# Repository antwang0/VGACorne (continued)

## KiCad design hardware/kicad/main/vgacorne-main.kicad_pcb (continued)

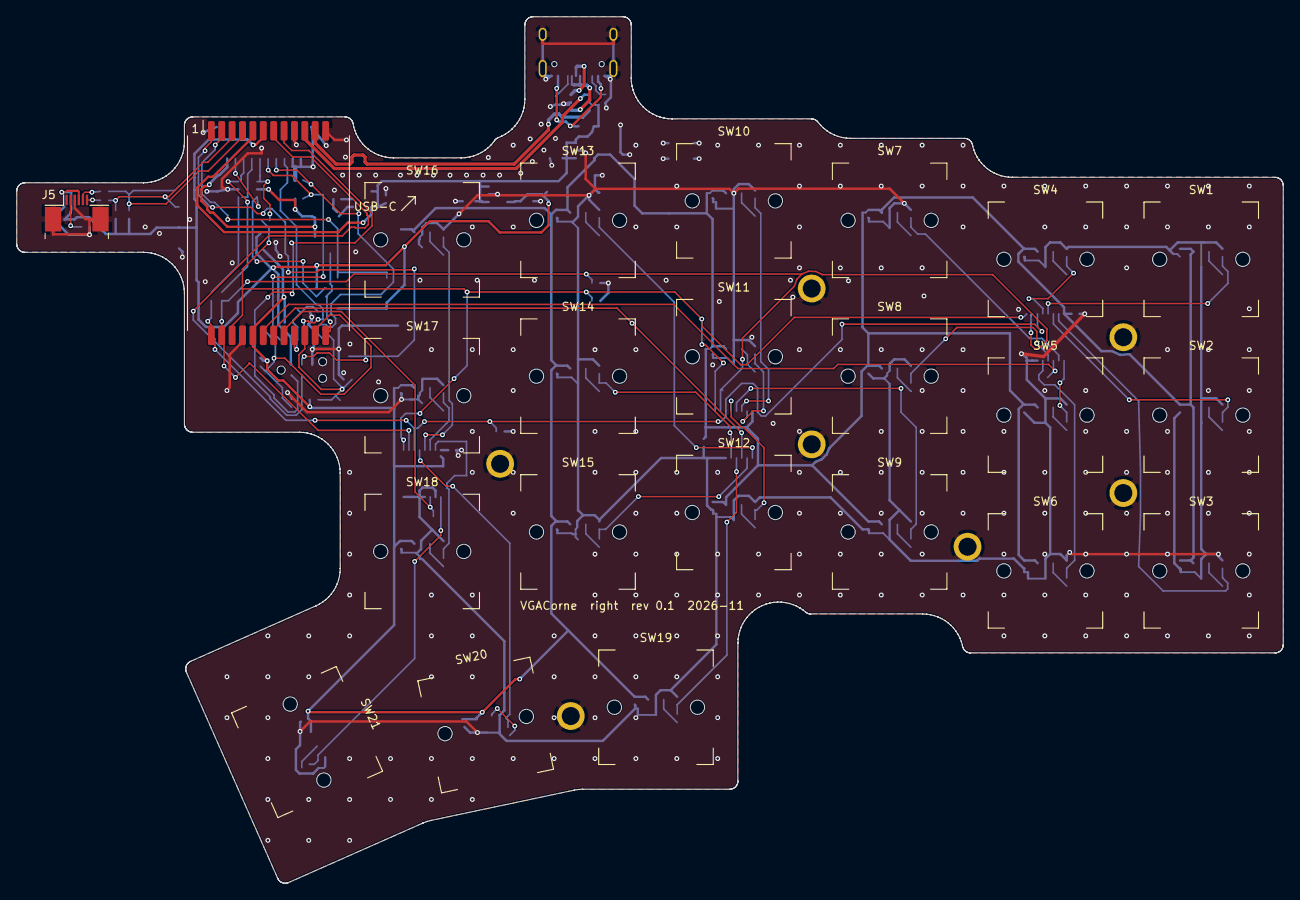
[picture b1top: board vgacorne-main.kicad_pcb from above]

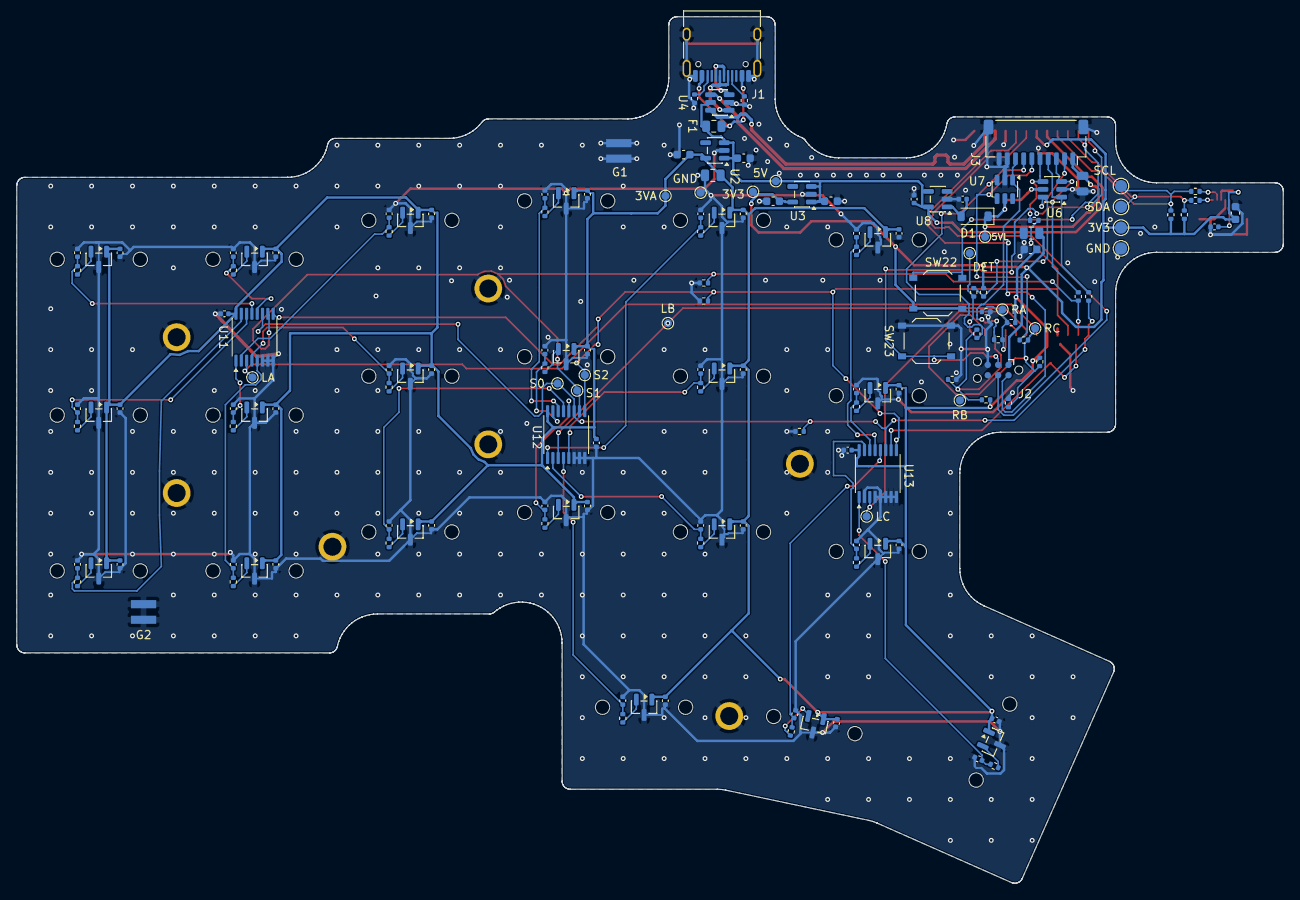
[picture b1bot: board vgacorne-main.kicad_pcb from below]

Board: 2 copper layers, 154.9 x 105.9 mm, 189 parts (159 on the bottom side), 81 nets.

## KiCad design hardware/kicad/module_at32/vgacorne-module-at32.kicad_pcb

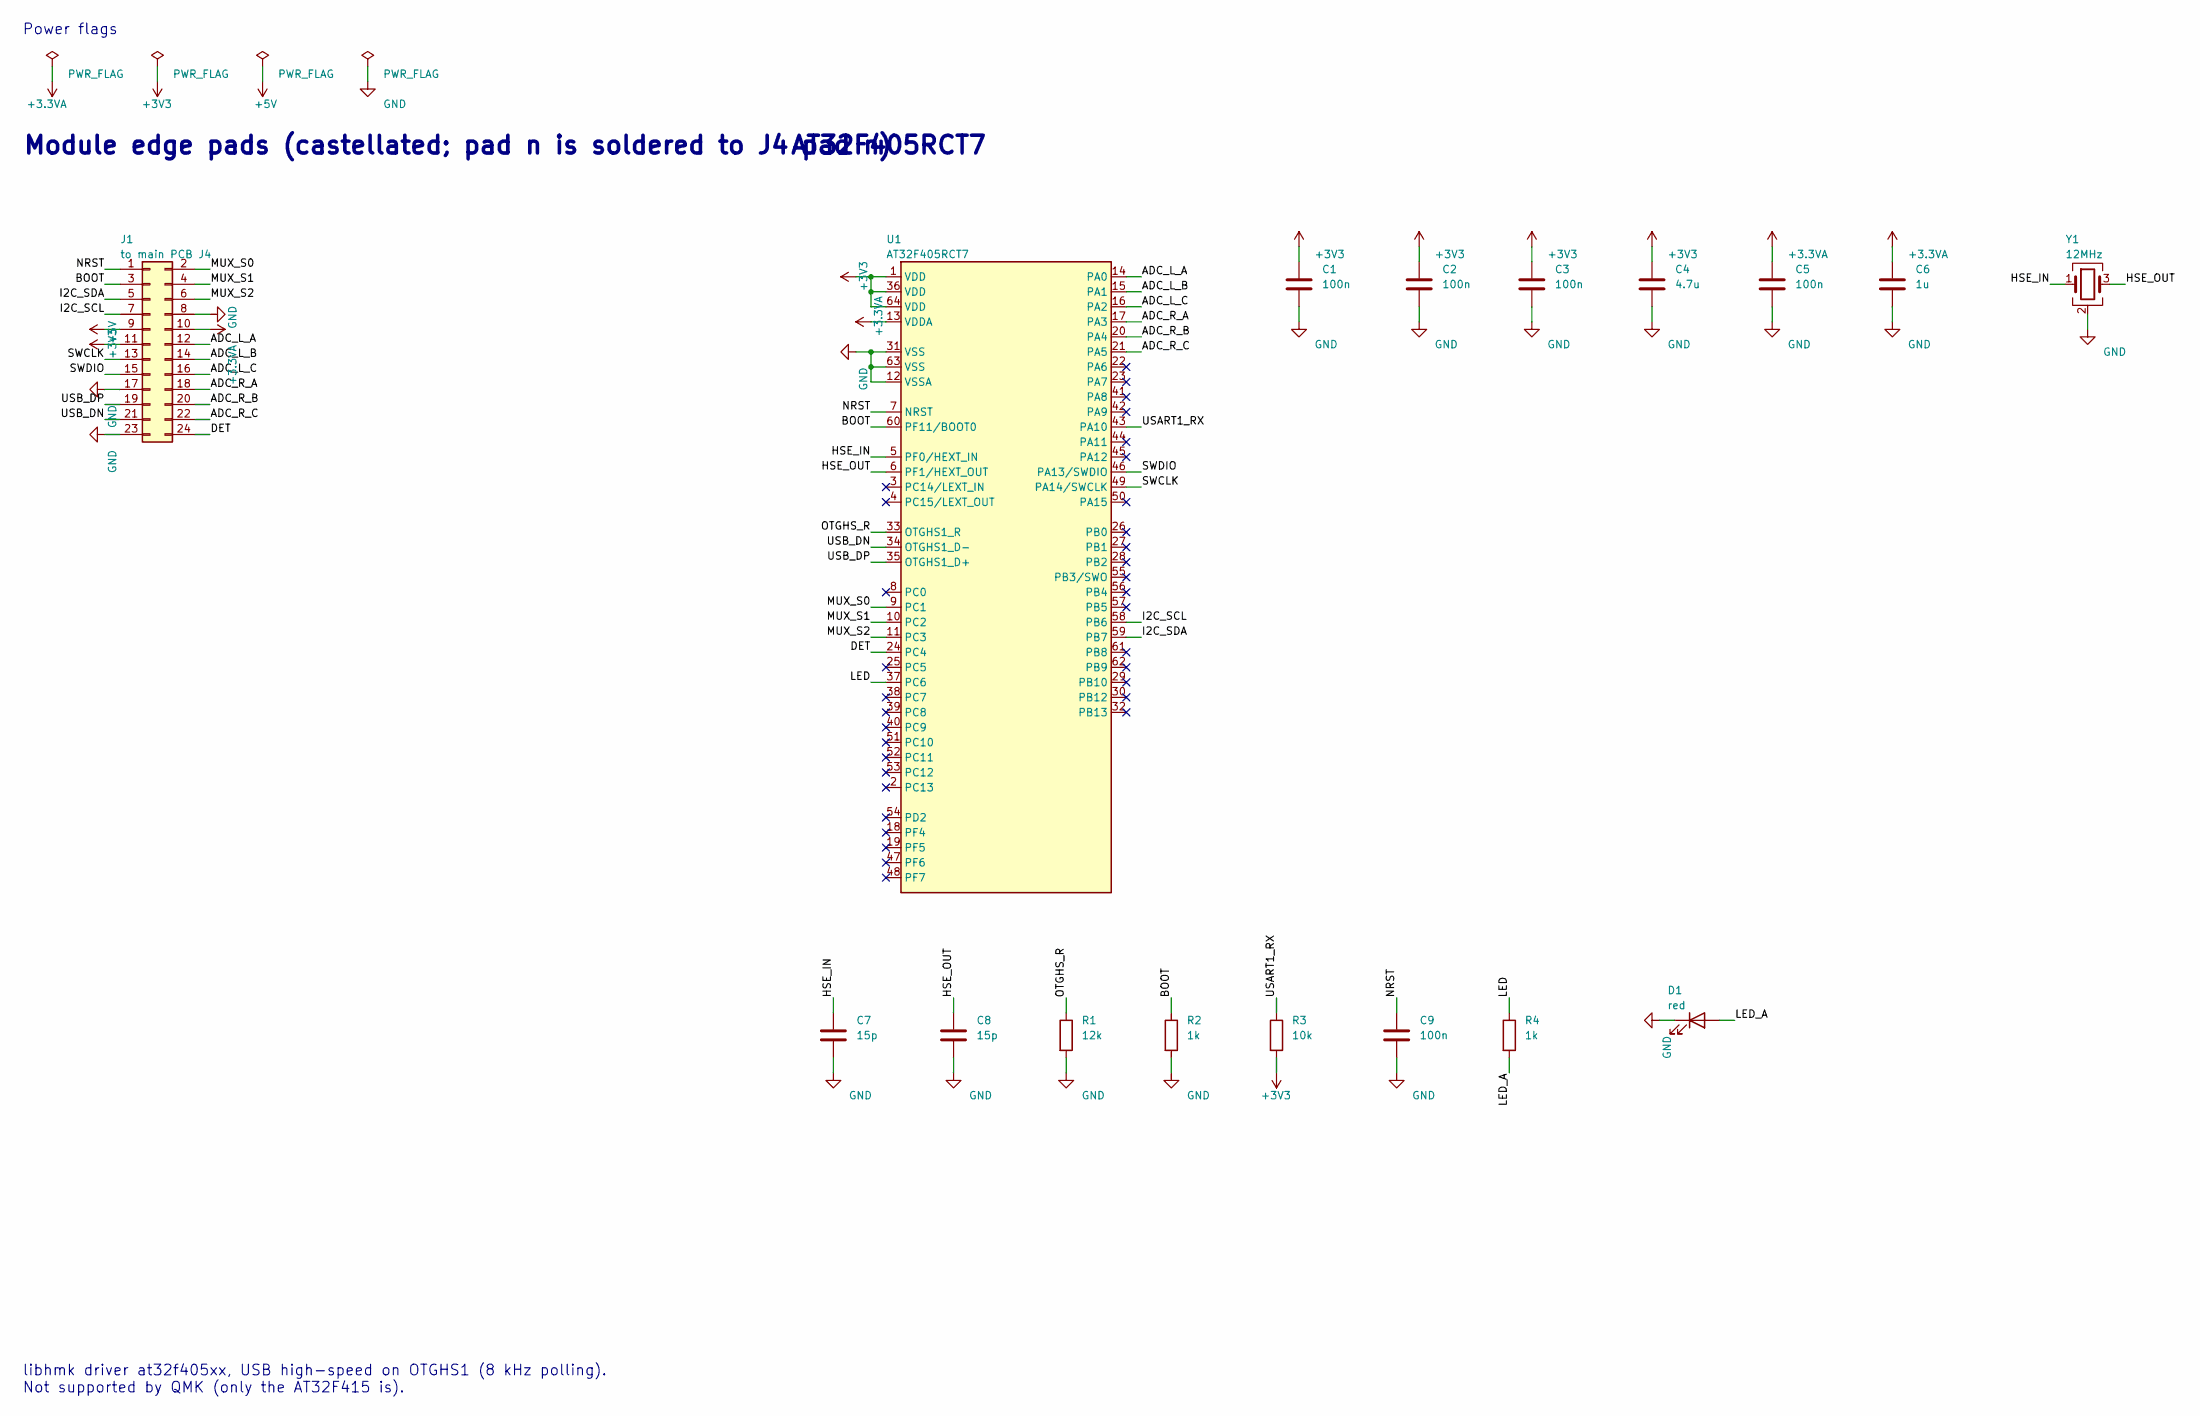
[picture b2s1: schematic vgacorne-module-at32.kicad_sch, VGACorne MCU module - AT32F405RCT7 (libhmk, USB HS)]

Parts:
C1, C2, C3, C5, C9: 100n; C_0402_1005Metric
C4: 4.7u; C_0603_1608Metric
C6: 1u; C_0603_1608Metric
C7, C8: 15p; C_0402_1005Metric
D1: red; LED_0603_1608Metric; MPN KT-0603R
J1: to main PCB J4; Module_Castellated_2x12_P1.27mm_19.4x25mm
R1: 12k; R_0402_1005Metric; Tolerance 1%
R2, R4: 1k; R_0402_1005Metric
R3: 10k; R_0402_1005Metric
U1: AT32F405RCT7; LQFP-64_10x10mm_P0.5mm; MPN AT32F405RCT7
Y1: 12MHz; Crystal_SMD_3225-4Pin_3.2x2.5mm; MPN X322512MOB4SI

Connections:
+3.3VA: C5.1, C6.1, J1.10, U1.13 (VDDA)
+3V3: C1.1, C2.1, C3.1, C4.1, J1.11, R3.2, U1.1 (VDD), U1.36 (VDD), U1.64 (VDD)
+5V: J1.9
/ADC_L_A: J1.12, U1.14 (PA0)
/ADC_L_B: J1.14, U1.15 (PA1)
/ADC_L_C: J1.16, U1.16 (PA2)
/ADC_R_A: J1.18, U1.17 (PA3)
/ADC_R_B: J1.20, U1.20 (PA4)
/ADC_R_C: J1.22, U1.21 (PA5)
/BOOT: J1.3, R2.1, U1.60 (PF11/BOOT0)
/DET: J1.24, U1.24 (PC4)
/HSE_IN: C7.1, U1.5 (PF0/HEXT_IN), Y1.1
/HSE_OUT: C8.1, U1.6 (PF1/HEXT_OUT), Y1.3
/I2C_SCL: J1.7, U1.58 (PB6)
/I2C_SDA: J1.5, U1.59 (PB7)
/LED: R4.1, U1.37 (PC6)
/LED_A: D1.2 (A), R4.2
/MUX_S0: J1.2, U1.9 (PC1)
/MUX_S1: J1.4, U1.10 (PC2)
/MUX_S2: J1.6, U1.11 (PC3)
/NRST: C9.1, J1.1, U1.7 (NRST)
/OTGHS_R: R1.1, U1.33 (OTGHS1_R)
/SWCLK: J1.13, U1.49 (PA14/SWCLK)
/SWDIO: J1.15, U1.46 (PA13/SWDIO)
/USART1_RX: R3.1, U1.43 (PA10)
/USB_DN: J1.21, U1.34 (OTGHS1_D-)
/USB_DP: J1.19, U1.35 (OTGHS1_D+)
GND: C1.2, C2.2, C3.2, C4.2, C5.2, C6.2, C7.2, C8.2, C9.2, D1.1 (K), J1.8, J1.17, J1.23, R1.2, R2.2, U1.12 (VSSA), U1.31 (VSS), U1.63 (VSS), Y1.2 (G), Y1.4 (G)

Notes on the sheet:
Module edge pads (castellated; pad n is soldered to J4 pad n)
AT32F405RCT7
libhmk driver at32f405xx, USB high-speed on OTGHS1 (8 kHz polling). Not supported by QMK (only the AT32F415 is).
Power flags

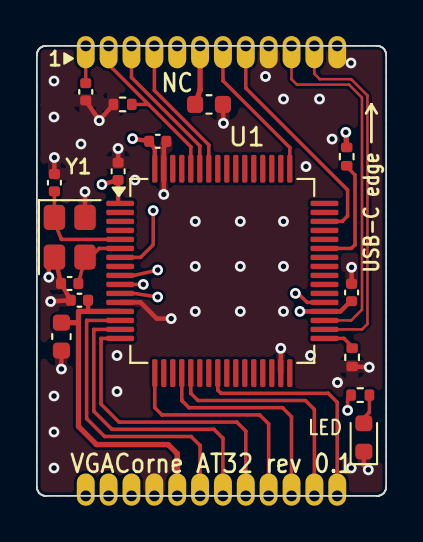
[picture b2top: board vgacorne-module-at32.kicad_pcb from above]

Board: 4 copper layers, 19.4 x 25.0 mm, 17 parts (0 on the bottom side), 27 nets.

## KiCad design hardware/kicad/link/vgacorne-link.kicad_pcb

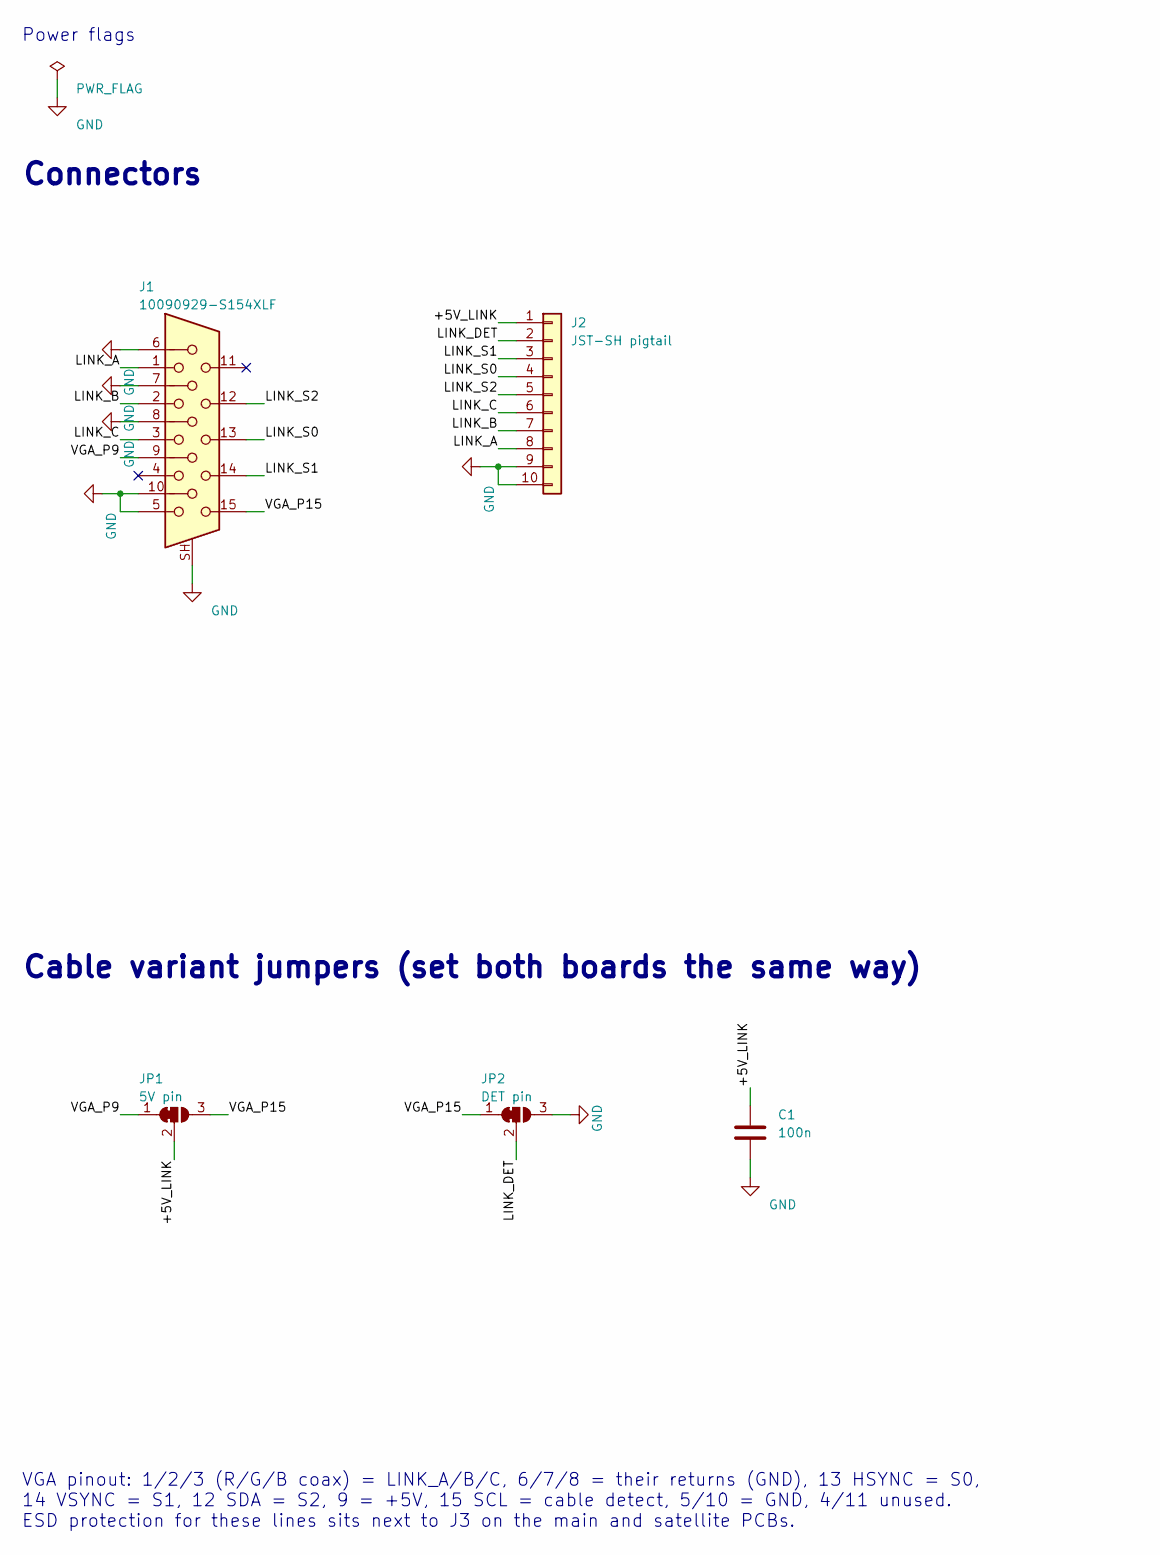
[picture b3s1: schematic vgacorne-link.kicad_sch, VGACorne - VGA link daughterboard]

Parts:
C1: 100n; C_0402_1005Metric
J1: 10090929-S154XLF; DSUB-15-HD_Socket_Vertical_P2.29x1.98mm_Amphenol_10090929; MPN Amphenol FCI 10090929-S154XLF
J2: JST-SH pigtail; WirePads_1x10_P1.6mm
JP1: 5V pin; SolderJumper-3_P1.3mm_Bridged12_RoundedPad1.0x1.5mm
JP2: DET pin; SolderJumper-3_P1.3mm_Bridged12_RoundedPad1.0x1.5mm

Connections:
/+5V_LINK: C1.1, J2.1, JP1.2 (C)
/LINK_A: J1.1, J2.8
/LINK_B: J1.2, J2.7
/LINK_C: J1.3, J2.6
/LINK_DET: J2.2, JP2.2 (C)
/LINK_S0: J1.13, J2.4
/LINK_S1: J1.14, J2.3
/LINK_S2: J1.12, J2.5
/VGA_P9: J1.9, JP1.1 (A)
/VGA_P15: J1.15, JP1.3 (B), JP2.1 (A)
GND: C1.2, J1.5, J1.6, J1.7, J1.8, J1.10, J1.SH, J2.9, J2.10, JP2.3 (B)

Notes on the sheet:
Connectors
Cable variant jumpers (set both boards the same way)
VGA pinout: 1/2/3 (R/G/B coax) = LINK_A/B/C, 6/7/8 = their returns (GND), 13 HSYNC = S0, 14 VSYNC = S1, 12 SDA = S2, 9 = +5V, 15 SCL = cable detect, 5/10 = GND, 4/11 unused. ESD protection for these lines sits next to J3 on the main and satellite PCBs.
Power flags

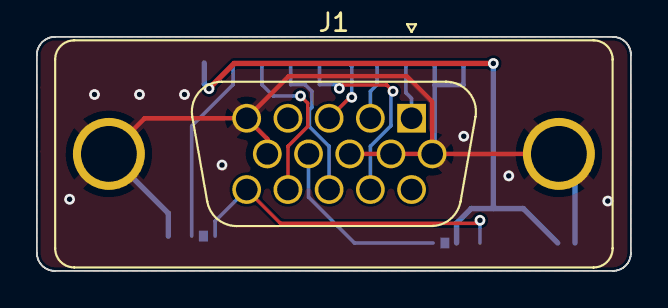
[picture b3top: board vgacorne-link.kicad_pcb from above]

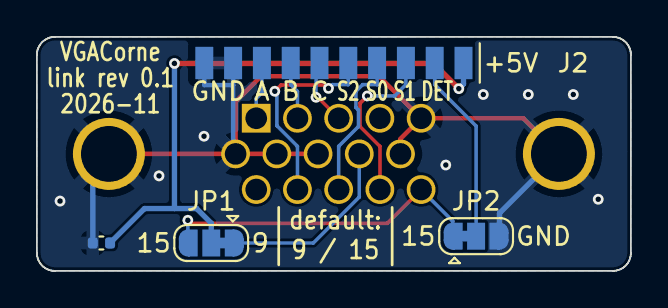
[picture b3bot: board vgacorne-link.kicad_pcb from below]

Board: 2 copper layers, 33.0 x 13.0 mm, 5 parts (4 on the bottom side), 11 nets.

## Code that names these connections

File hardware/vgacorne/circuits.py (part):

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# LQFP-64 pins used for keyboard signals. The AT32F405RCT7 and STM32F446RET6 share
# these pin numbers, so both modules (and their firmware configs) use the same map.
MCU_SIGNAL_PINS = {
    "14": "ADC_L_A", "15": "ADC_L_B", "16": "ADC_L_C",  # PA0..PA2: local muxes
    "17": "ADC_R_A", "20": "ADC_R_B", "21": "ADC_R_C",  # PA3..PA5: satellite muxes
    "9": "MUX_S0", "10": "MUX_S1", "11": "MUX_S2",  # PC1..PC3
    "24": "DET",  # PC4
    "7": "NRST", "60": "BOOT", "46": "SWDIO", "49": "SWCLK",  # NRST, BOOT0, PA13, PA14
    "58": "I2C_SCL", "59": "I2C_SDA",  # PB6/PB7: I2C1 (AF4 on the STM32, MUX4 on the AT32)
    "37": "LED",  # PC6 (TIM3_CH1 / TMR3_CH1): the module's status LED, lit when high
}
# firmware.py derives libhmk's select/input pin names from these by tracing the netlists.

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

def status_led(block="mcu") -> list[Part]:
    """On each MCU module: a red LED on PC6 for the firmware (QMK: caps lock).
    It is under the trackpad once that is fitted, so it is a bring-up aid."""
    return [
        R("R4", "1k", "LED", "LED_A", block, description="Status LED: 1.3 mA"),
        Part("D1", "Device:LED", "red", "LED_SMD:LED_0603_1608Metric", {"A": "LED_A", "K": "GND"}, block,
             fields={"MPN": "KT-0603R"}, description="Status LED on PC6, lit when the pin is high"),
    ]


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        R("R19", "4.7k", "I2C_SCL", "+3V3", "trackpad"),
        R("R20", "4.7k", "I2C_SDA", "+3V3", "trackpad"),
        # Series resistors at the connector: the pad sits under a hand, behind a thin overlay
        R("R24", "100", "I2C_SCL", "TP_SCL", "trackpad", description="ESD: limits current into the MCU's I2C pins"),
        R("R25", "100", "I2C_SDA", "TP_SDA", "trackpad"),
        C("C16", "1u", "+3V3", "GND", "trackpad", fp=C0603),
    ]
    if "TP_NRST" in PAD.connector_pins.values():  # internal pull-up; Azoteq recommends 100 nF
        p.append(C("C17", "100n", "TP_NRST", "GND", "trackpad"))
    # Link to the satellite (via the VGA daughterboard)
    pull_up = SENSOR.invert_adc  # pull toward "released" when the cable is absent
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        R("R16", "100k", "ADC_R_C", "GND", "link", dnp=pull_up),
        R("R17", "10k", "LINK_DET", "+3V3", "link"),
        R("R18", "1k", "LINK_DET", "DET", "link"),
        # The MCU leaves PC1-PC3 floating through reset and DFU; hold the six muxes' selects low
        *[R(f"R{21 + i}", "100k", f"MUX_S{i}", "GND", "link",
            description="Select line idles low while the MCU is in reset or DFU" if i == 0 else None) for i in range(3)],
        # TPS2051C (SLVSAU6I 8.2.2.1): >= 10 uF ceramic where the output drives a cable
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        Part("JP1", "Jumper:SolderJumper_3_Bridged12", "5V pin", "Jumper:SolderJumper-3_P1.3mm_Bridged12_RoundedPad1.0x1.5mm",
             {"1": "VGA_P9", "2": "+5V_LINK", "3": "VGA_P15"}, "jumpers",
             description="+5 V on VGA pin 9 (default) or pin 15 (for 3+4 cables without pin 9)"),
        Part("JP2", "Jumper:SolderJumper_3_Bridged12", "DET pin", "Jumper:SolderJumper-3_P1.3mm_Bridged12_RoundedPad1.0x1.5mm",
             {"1": "VGA_P15", "2": "LINK_DET", "3": "GND"}, "jumpers",
             description="Cable-detect on VGA pin 15 (default), or tied to GND (always connected) when "
                         "JP1 moves +5 V to pin 15"),
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        ("jumpers", "Cable variant jumpers (set both boards the same way)", (20.32, 150.0), 250),
    ]
    notes = [
        ("VGA pinout: 1/2/3 (R/G/B coax) = LINK_A/B/C, 6/7/8 = their returns (GND), 13 HSYNC = S0,\n"
         "14 VSYNC = S1, 12 SDA = S2, 9 = +5V, 15 SCL = cable detect, 5/10 = GND, 4/11 unused.\n"
         "ESD protection for these lines sits next to J3 on the main and satellite PCBs.", (20.32, 230.0)),
    ]
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          fields={"Tolerance": "1%"}),
        R("R2", "1k", "BOOT", "GND", "mcu", description="BOOT0 pull-down (DS v2.02 Table 9 note 7: 3.3k or less)"),
        R("R3", "10k", "USART1_RX", "+3V3", "mcu",
          description="Holds the ROM bootloader's USART1 RX (PA10) idle so noise can't select it over USB"),
        C("C9", "100n", "NRST", "GND", "mcu"),
        *status_led(),
    ]
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        R("R2", "10k", "BOOT1", "GND", "mcu",
          description="PB2/BOOT1 pull-down: BOOT0 = 1 only reaches the DFU bootloader with BOOT1 = 0 (RM0390)"),
        R("R3", "10k", "USART1_RX", "+3V3", "mcu",
          description="Holds the bootloader's unused USART1 RX (PA10) idle so noise can't select it (AN2606)"),
        C("C11", "100n", "NRST", "GND", "mcu"),
        *status_led(),
    ]
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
